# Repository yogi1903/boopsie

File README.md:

# boopsiev1
Macropad design files

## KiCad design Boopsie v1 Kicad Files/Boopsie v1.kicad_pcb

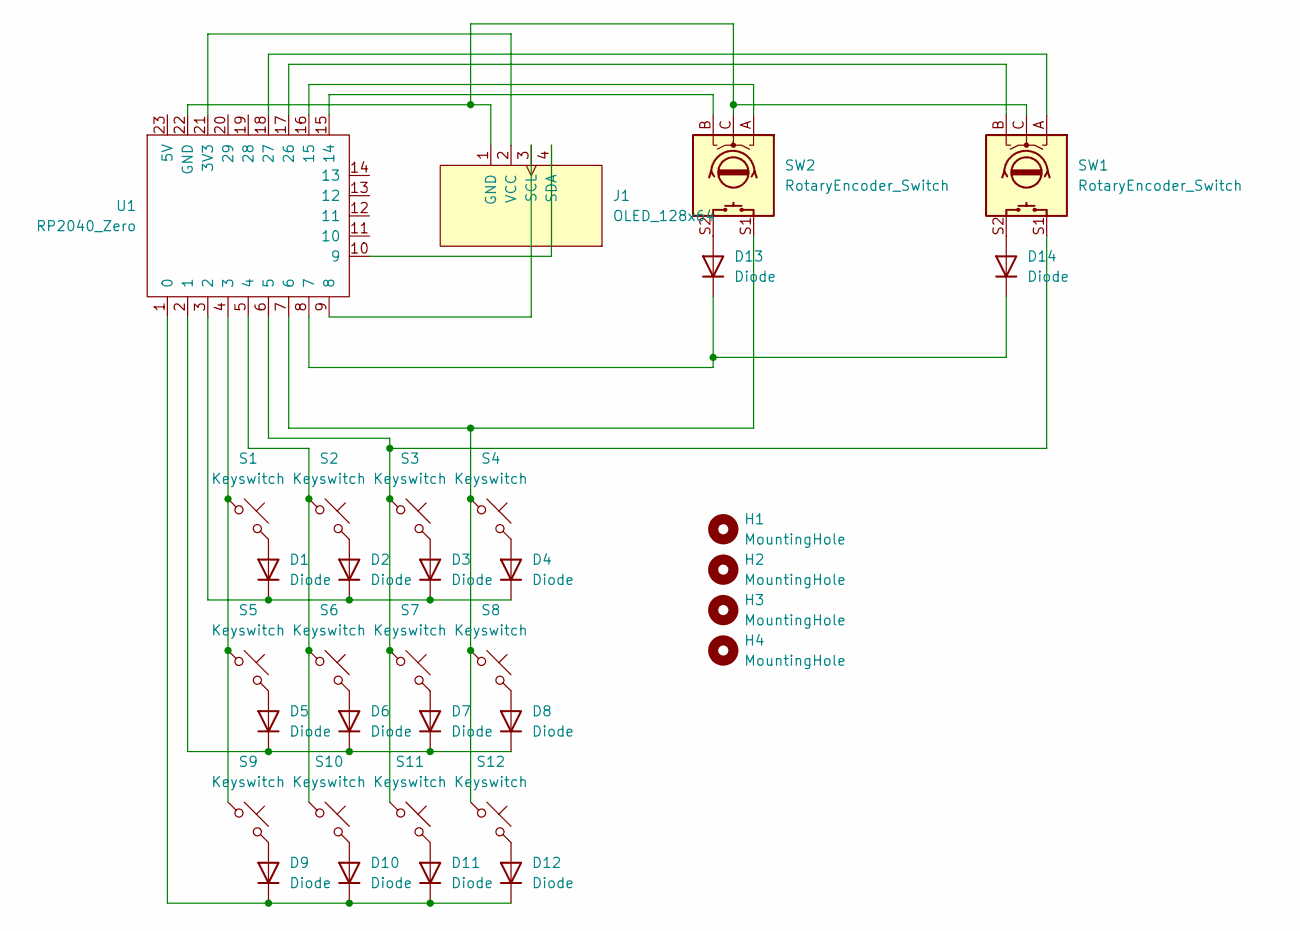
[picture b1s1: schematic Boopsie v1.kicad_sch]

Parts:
D1, D2, D3, D4, D5, D6, D7, D8, D9, D10, D11, D12, D13, D14: Diode; Diode_DO-35
H1, H2, H3, H4: MountingHole; MountingHole_2.2mm_M2
J1: OLED_128x64
S1, S2, S3, S4, S5, S6, S7, S8, S9, S10, S11, S12: Keyswitch; Hotswap_MX_1.00u
SW1, SW2: RotaryEncoder_Switch; RotaryEncoder_Alps_EC11E-Switch_Vertical_H20mm
U1: RP2040_Zero

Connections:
unnamed: D1.2 (A), S1.2
unnamed: D1.1 (K), D2.1 (K), D3.1 (K), D4.1 (K), U1.3 (2)
unnamed: D2.2 (A), S2.2
unnamed: D3.2 (A), S3.2
unnamed: D4.2 (A), S4.2
unnamed: D5.2 (A), S5.2
unnamed: D5.1 (K), D6.1 (K), D7.1 (K), D8.1 (K), U1.2 (1)
unnamed: D6.2 (A), S6.2
unnamed: D7.2 (A), S7.2
unnamed: D8.2 (A), S8.2
unnamed: D9.2 (A), S9.2
unnamed: D10.2 (A), S10.2
unnamed: D9.1 (K), D10.1 (K), D11.1 (K), D12.1 (K), U1.1 (0)
unnamed: D11.2 (A), S11.2
unnamed: D12.2 (A), S12.2
unnamed: D13.2 (A), SW2.S2
unnamed: D13.1 (K), D14.1 (K), U1.8 (7)
unnamed: D14.2 (A), SW1.S2
unnamed: J1.1 (GND), SW1.C, SW2.C, U1.22 (GND)
unnamed: J1.3 (SCL), U1.9 (8)
unnamed: J1.4 (SDA), U1.10 (9)
unnamed: J1.2 (VCC), U1.21 (3V3)
unnamed: S1.1, S5.1, S9.1, U1.4 (3)
unnamed: S2.1, S6.1, S10.1, U1.5 (4)
unnamed: S3.1, S7.1, S11.1, SW1.S1, U1.6 (5)
unnamed: S4.1, S8.1, S12.1, SW2.S1, U1.7 (6)
unnamed: SW2.B, U1.15 (14)
unnamed: SW2.A, U1.16 (15)
unnamed: SW1.B, U1.17 (26)
unnamed: SW1.A, U1.18 (27)

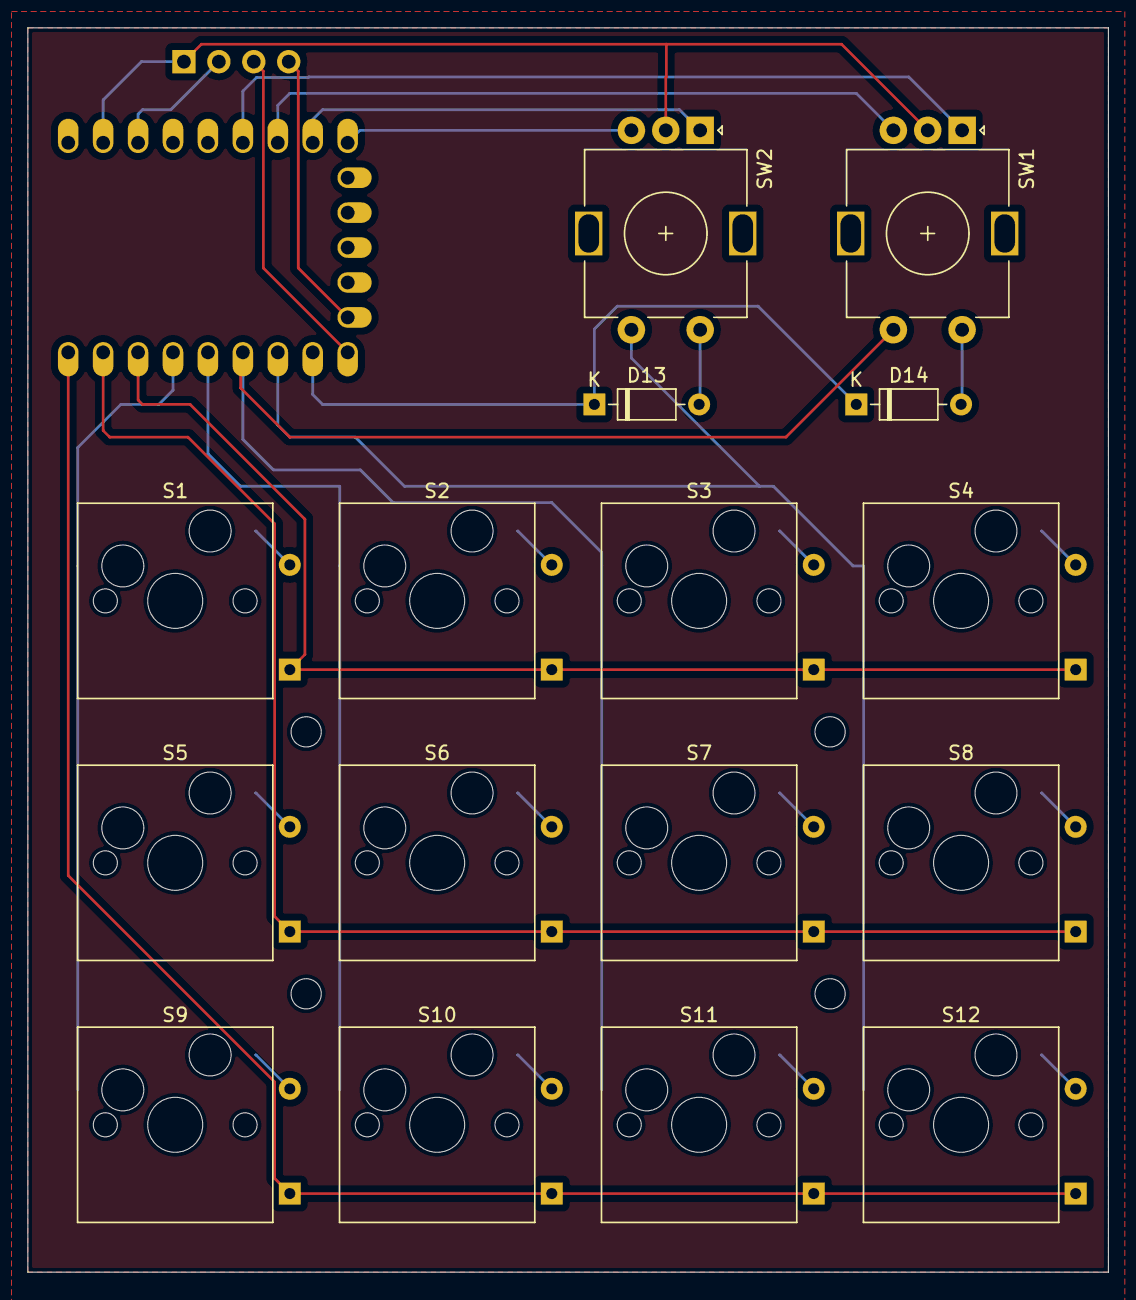
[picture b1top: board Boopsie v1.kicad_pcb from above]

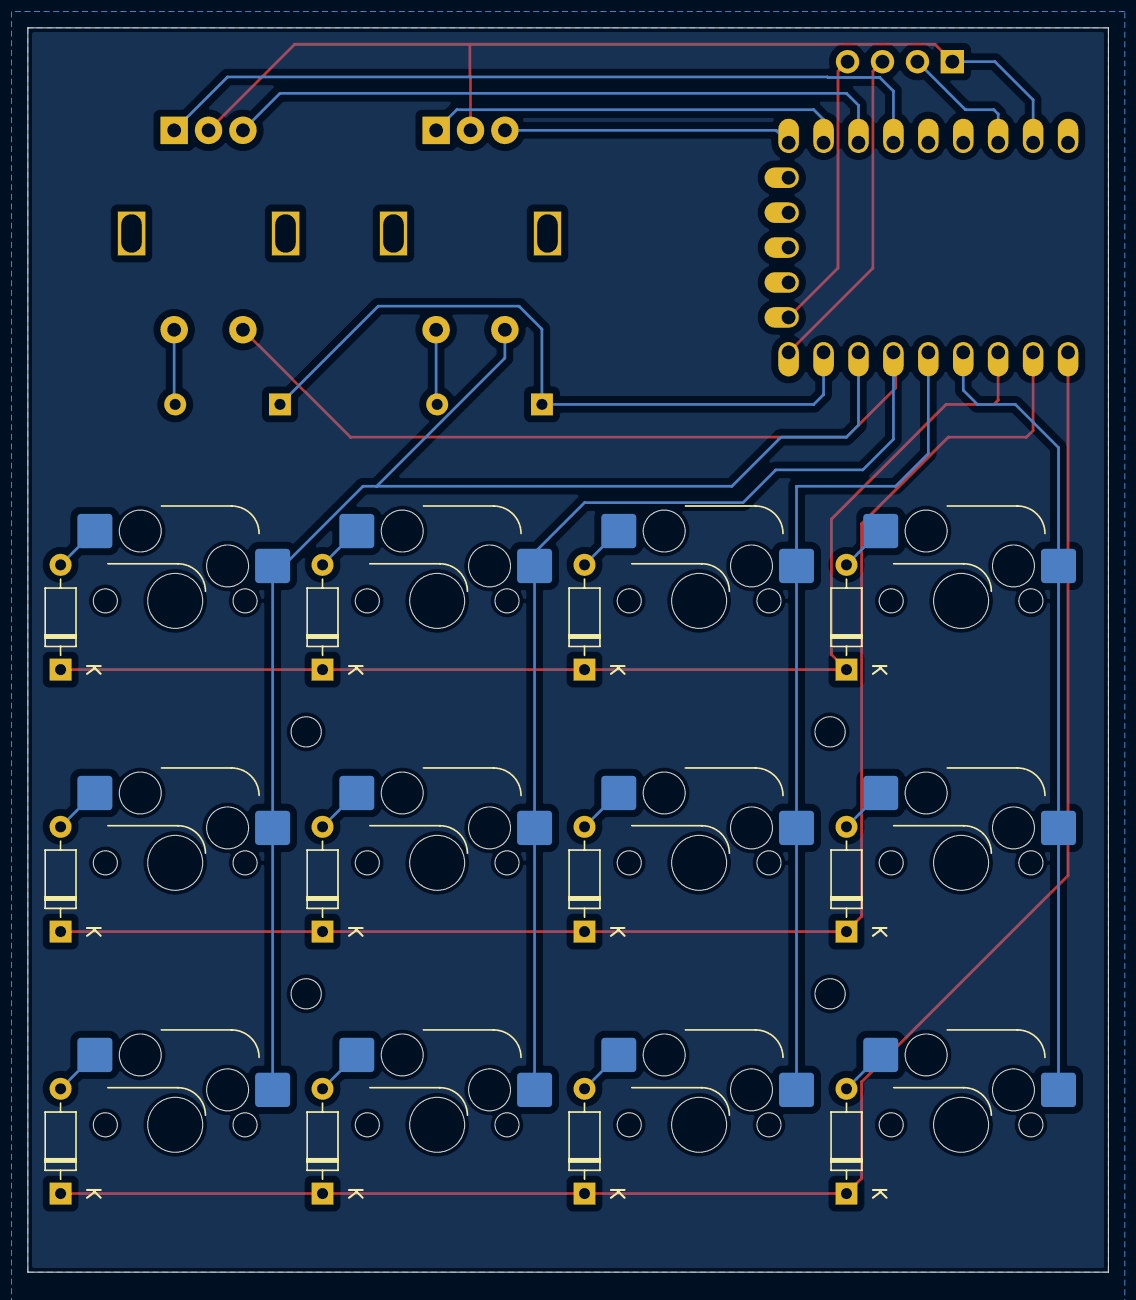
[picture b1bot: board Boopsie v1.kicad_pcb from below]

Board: 2 copper layers, 78.6 x 90.5 mm, 34 parts (13 on the bottom side), 30 nets.

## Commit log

2024-03-09 Boopsie v1 pcb and schematics
2024-03-09 pcb update
2024-03-09 sch and pcb updates
2024-03-09 final pcb update :deadge:
2024-03-09 idk what's going on help me pls
2024-03-09 final final
2024-03-09 final final final
2024-03-10 traces refined
2024-03-10 final trace refinement
2024-03-20 3d models
2024-03-20 sizing changes
